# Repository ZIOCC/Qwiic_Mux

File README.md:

# Zio Qwiic Mux

> This product can be available for purchase [here](https://www.smart-prototyping.com/Zio-Qwiic-Mux.html).

#### Description

This board is awesome. It lets you switch between sets of Qwiic device chains that are isolated from one another.

That means that you can use up to eight of an I2C device that has a fixed address. And because this board has eight address option itself, you can actually control many more than that.

> The schematic for our Qwiic Mux board is a derivative of the [Adafruit TCA9548A 1-to-8 I2C Multiplexer Breakout](https://learn.adafruit.com/adafruit-tca9548a-1-to-8-i2c-multiplexer-breakout/overview).

One of the limitations of I2C, on which Qwiic is based, is that some sensors only have one or two changeable bits in their address. Some even have a single fixed address. That means that you can’t use more than one of them connected to the same I2C bus on your microcontroller. What if you want to use more than one? Thanks to the handy-dandy Zio Qwiic MUX, you can use up to EIGHT of that fixed-address TOF range-finder module that you want to stick on every side of your drone for automatic collision avoidance. Your shattered dreams of building an I2C-based motion capture suit using BNO080 breakouts? Shattered no more, my friend. We’ve got your sixteen sensors right here.

What’s the trick? The TCA9548APWR is an eight-channel two-wire bus multiplexer. It is, in fact, an I2C device itself. By changing the value of one of the TCA9548APWR’s registers, you can route the connection from your MCU to any of eight pairs of pins, each with their own set of pullup resistors (optional, via solder jumpers), on the other side of this IC. It’s a lot like a railroad track switch. Want to know what else is cool about that? It overcomes the 4-foot wire-length limitation of Qwiic. Each one of those ports counts as a different bus.

We don’t do any voltage level shifting on these ports. Each and every one is an unadulterated 3.3v Qwiic port. The TCA9548APWR also has three configurable address bits, so you can use up to eight of them on the same bus. Or you can get really crazy and connect eight other Zio Qwiic MUX boards, all with the same address, to each of the eight ports on your first Zio Qwiic MUX. And then… well, exponents being what they are, you could split your one I2C bus into over sixteen million of them using only these boards. That is, if you had the money and space and inclination. Frankly speaking, we don’t recommend it. But if you want to place an order for the two million or so boards necessary to do it, we could probably work out some kind of volume discount for you. Just don’t ask us to offer a power supply solution for that.

#### Specification

* Weight: 2.6g (0.09oz)
* IC: TCA9548A
* I2C address: 0x70- 0x77
* Default:0x70

#### Links

* [TCA9548A datasheet](https://www.smart-prototyping.com/image/data/NOA-RnD/101900%20Mux/tca9548a.pdf)
* [Example Code- Connect two TOF sensor with Mux](https://www.smart-prototyping.com/image/data/NOA-RnD/101900%20Mux/Zio_Qwiic_Mux_TOF_Example_Code.zip)
* [Eagle files](https://github.com/ZIOCC/Qwiic_Mux)

##### Connections for example code

Adafruit also has a [great little tutorial](https://learn.adafruit.com/adafruit-tca9548a-1-to-8-i2c-multiplexer-breakout/wiring-and-test) with some very simple Arduino functions for using it, the most important being:
<pre>
<code>
#define TCAADDR 0x70
void tcaselect(uint8_t i) {
  if (i > 7) return;
  Wire.beginTransmission(TCAADDR);
  Wire.write(1 << i);
  Wire.endTransmission();
}
</code>
</pre>

Just drop that into your sketch and then call <code>tcaselect(x);</code> where x is the port, from 0 to 7, that you want to activate.

And to disable all of the ports (in the case that you're using more than one of these board, and need to prevent an address collision between identical devices connected to each) just call this function with that Qwiic Mux's address (set by soldering closed a combination of the A0, A1, and A2 jumpers on the bottom of the PCB) as the only argument:

<pre><code>
void tcadisable(uint8_t tcaaddress){<br>
  Wire.beginTransmission(tcaaddress);<br>
  Wire.write(0);  // no channel selected<br>
  Wire.endTransmission();<br>
}<br>
</code></pre>

> All Zio products are released under the [Creative Commons Attribution, Share-Alike License](https://creativecommons.org/licenses/by-sa/4.0/), and in accordance with the principles of the [Open Source Hardware Association's OSHW Statement of Principles 1.0 and OSHW Definition 1.0](https://www.oshwa.org/definition/).

> ###### About Zio
> Zio is a new line of open sourced, compact, and grid layout boards, fully integrated for Arduino and Qwiic ecosystem. Designed ideally for wearables, robotics, small-space limitations or other on the go projects. Check out other awesome Zio products [here](https://www.smart-prototyping.com/Zio).

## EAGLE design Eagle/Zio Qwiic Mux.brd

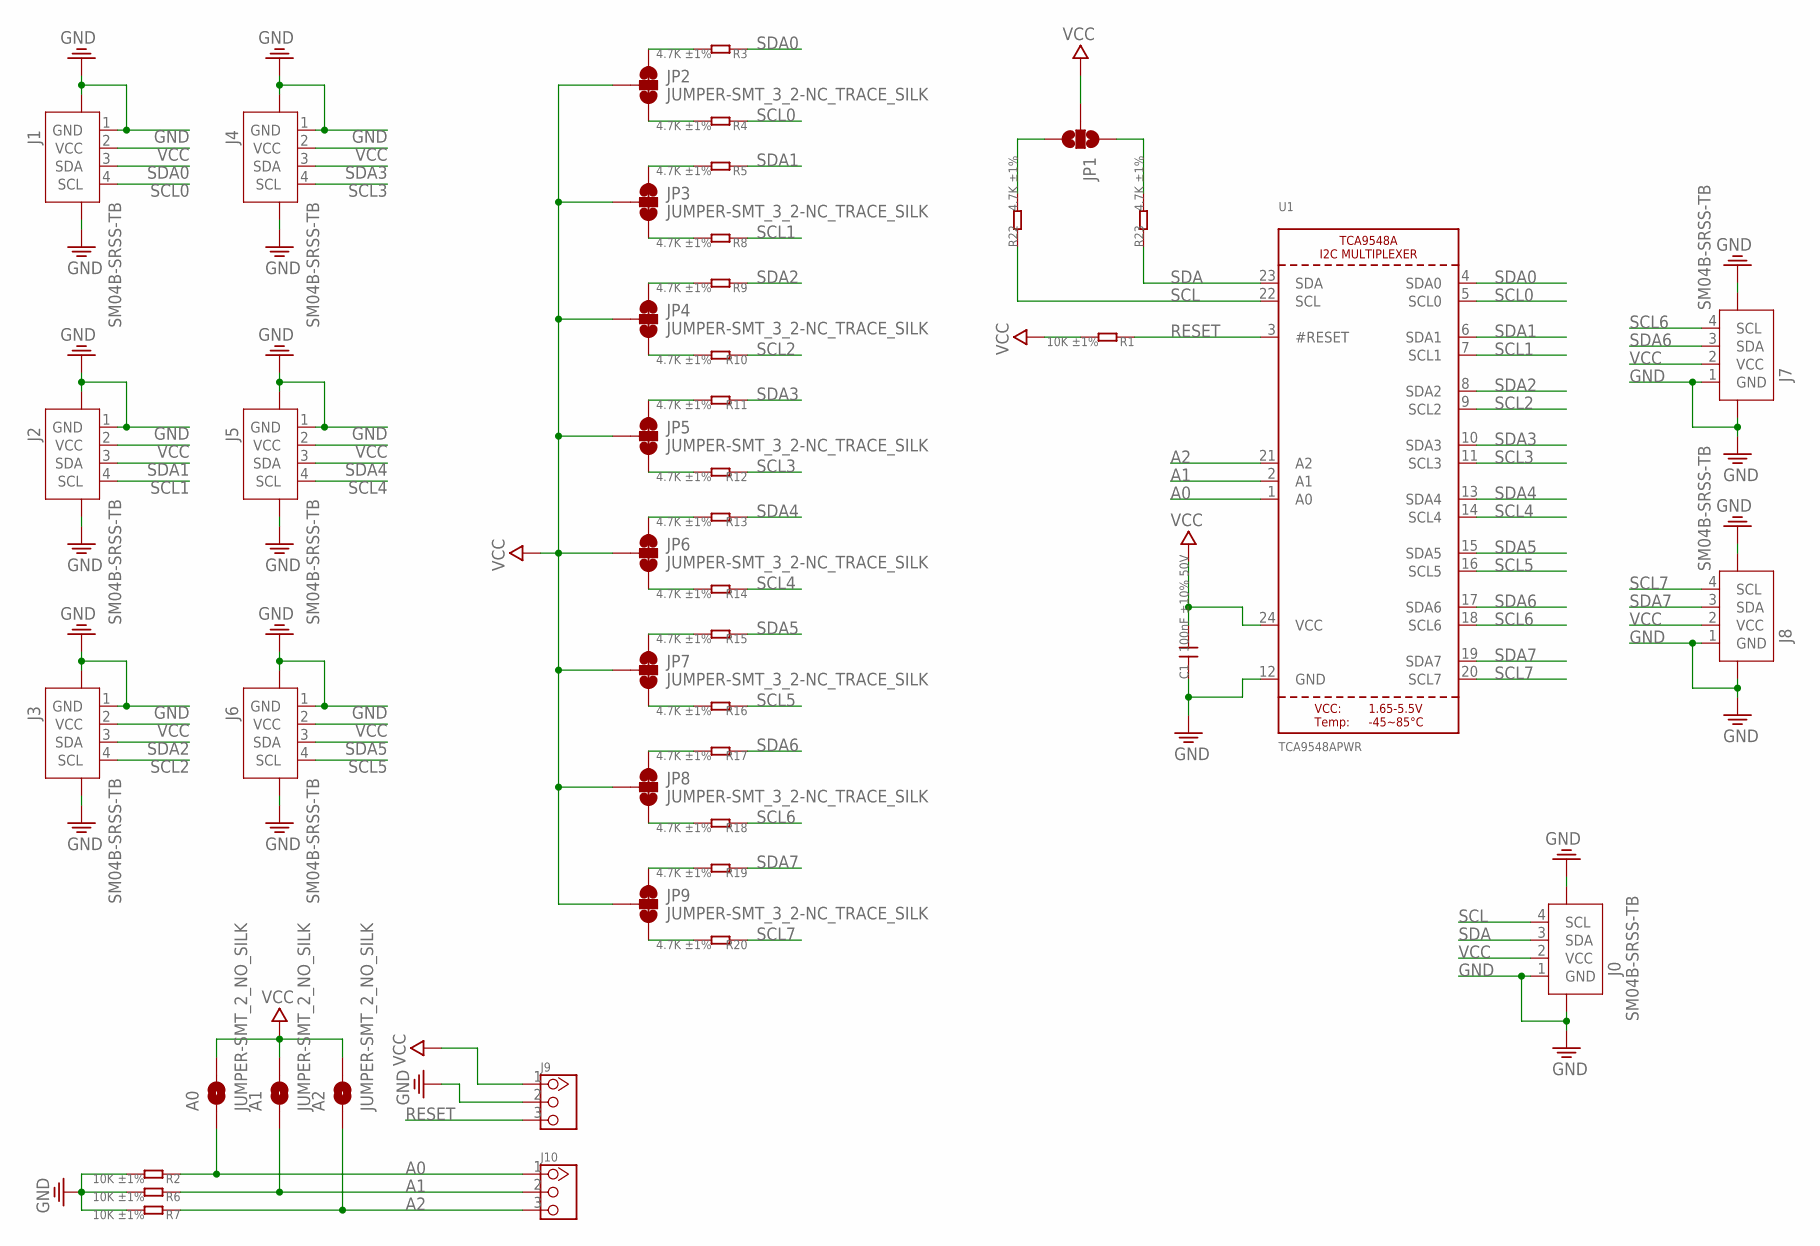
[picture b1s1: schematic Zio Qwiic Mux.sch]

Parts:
A0, A1, A2: JUMPER-SMT_2_NO_SILK; SMT-JUMPER_2_NO_SILK
C1: 100nF ±10% 50V; 0603
J0, J1, J2, J3, J4, J5, J6, J7, J8: SM04B-SRSS-TB; JST-SH-4P
J9, J10: HEADER-3P-2.54; 3P-2.54
JP1: JUMPER-SMT_3_2-NC_PASTE_NOCREM; SMT-JUMPER_3_2-NC_PASTE_SILK_NOCREM
JP2, JP3, JP4, JP5, JP6, JP7, JP8, JP9: JUMPER-SMT_3_2-NC_TRACE_SILK; SMT-JUMPER_3_2-NC_TRACE_SILK
R1, R2, R6, R7: 10K ±1%; 0402
R3, R4, R5, R8, R9, R10, R11, R12, R13, R14, R15, R16, R17, R18, R19, R20, R22, R23: 4.7K ±1%; 0402
U1: TCA9548APWR; TSSOP24

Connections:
A0: A0.1, J10.1, R2.1, U1.1 (A0)
A1: A1.1, J10.2, R6.1, U1.2 (A1)
A2: A2.1, J10.3, R7.1, U1.21 (A2)
GND: C1.1, J0.1 (GND), J0.NC1 (5), J0.NC2 (6), J1.1 (GND), J1.NC1 (5), J1.NC2 (6), J2.1 (GND), J2.NC1 (5), J2.NC2 (6), J3.1 (GND), J3.NC1 (5), J3.NC2 (6), J4.1 (GND), J4.NC1 (5), J4.NC2 (6), J5.1 (GND), J5.NC1 (5), J5.NC2 (6), J6.1 (GND), J6.NC1 (5), J6.NC2 (6), J7.1 (GND), J7.NC1 (5), J7.NC2 (6), J8.1 (GND), J8.NC1 (5), J8.NC2 (6), J9.2, R2.2, R6.2, R7.2, U1.12 (GND)
unnamed: JP2.1, R3.2
unnamed: JP2.3, R4.2
unnamed: JP3.1, R5.2
unnamed: JP3.3, R8.2
unnamed: JP4.1, R9.2
unnamed: JP4.3, R10.2
unnamed: JP5.1, R11.2
unnamed: JP5.3, R12.2
unnamed: JP1.3, R22.2
unnamed: JP1.1, R23.2
unnamed: JP6.1, R13.2
unnamed: JP6.3, R14.2
unnamed: JP7.1, R15.2
unnamed: JP7.3, R16.2
unnamed: JP8.1, R17.2
unnamed: JP8.3, R18.2
unnamed: JP9.1, R19.2
unnamed: JP9.3, R20.2
RESET: J9.3, R1.1, U1.3 (#RESET)
SCL: J0.4 (SCL), R22.1, U1.22 (SCL)
SCL0: J1.4 (SCL), R4.1, U1.5 (SCL0)
SCL1: J2.4 (SCL), R8.1, U1.7 (SCL1)
SCL2: J3.4 (SCL), R10.1, U1.9 (SCL2)
SCL3: J4.4 (SCL), R12.1, U1.11 (SCL3)
SCL4: J5.4 (SCL), R14.1, U1.14 (SCL4)
SCL5: J6.4 (SCL), R16.1, U1.16 (SCL5)
SCL6: J7.4 (SCL), R18.1, U1.18 (SCL6)
SCL7: J8.4 (SCL), R20.1, U1.20 (SCL7)
SDA: J0.3 (SDA), R23.1, U1.23 (SDA)
SDA0: J1.3 (SDA), R3.1, U1.4 (SDA0)
SDA1: J2.3 (SDA), R5.1, U1.6 (SDA1)
SDA2: J3.3 (SDA), R9.1, U1.8 (SDA2)
SDA3: J4.3 (SDA), R11.1, U1.10 (SDA3)
SDA4: J5.3 (SDA), R13.1, U1.13 (SDA4)
SDA5: J6.3 (SDA), R15.1, U1.15 (SDA5)
SDA6: J7.3 (SDA), R17.1, U1.17 (SDA6)
SDA7: J8.3 (SDA), R19.1, U1.19 (SDA7)
VCC: A0.2, A1.2, A2.2, C1.2, J0.2 (VCC), J1.2 (VCC), J2.2 (VCC), J3.2 (VCC), J4.2 (VCC), J5.2 (VCC), J6.2 (VCC), J7.2 (VCC), J8.2 (VCC), J9.1, JP1.2, JP2.2, JP3.2, JP4.2, JP5.2, JP6.2, JP7.2, JP8.2, JP9.2, R1.2, U1.24 (VCC)

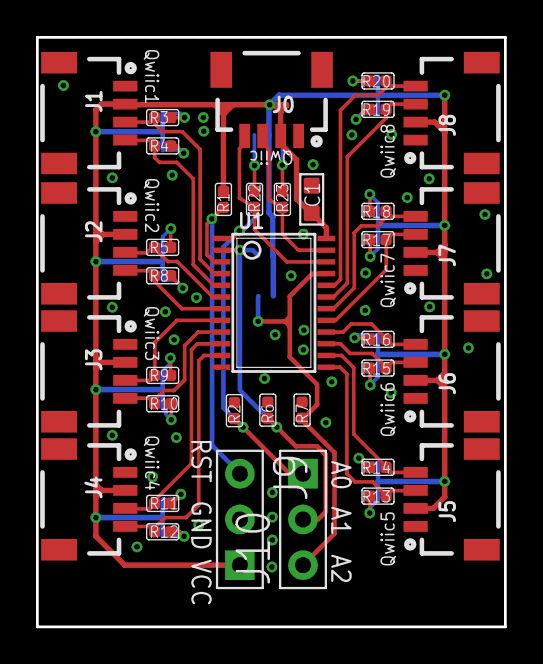
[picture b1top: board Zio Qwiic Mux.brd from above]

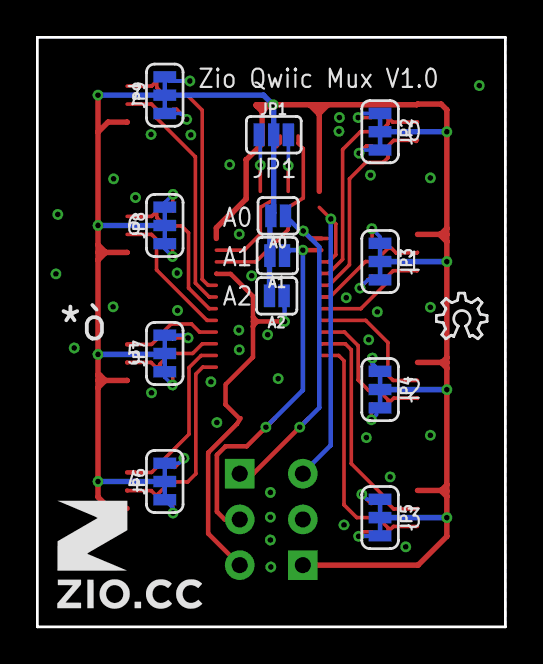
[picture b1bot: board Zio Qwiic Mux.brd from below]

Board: 2 copper layers, 26.0 x 32.8 mm, 49 parts (14 on the bottom side), 42 nets.

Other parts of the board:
U$7: 6MM
U$8: OSHW_6X100_NOTEXT

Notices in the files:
parts and their libraries:
microbuilder: This work is placed in the public domain, and may be freely used for commercial and non-commercial work with the following conditions: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
SparkFun-Jumpers: Licensing: Creative Commons ShareAlike 4.0 International - https://creativecommons.org/licenses/by-sa/4.0
